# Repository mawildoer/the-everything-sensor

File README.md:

# The Everything Sensor!

A collective dev board for all the things our hearts desired.

## Features

 - BME280 (Temperature, Humidity, Pressure)
 - LIS2DH12TR (Accelerometer)
 - TMC2209 (Stepper Motor Driver)
 - HX711 (Load Cell Amplifier)
 - ATGM336H_5N31 (GPS)
 - SGP40_D_R4 (VOC Sensor)
 - MAX31856MUDT (Thermocouple Amplifier)
 - NAU7802 (Load Cell Amplifier)
 - TCA9548APWR (I2C Multiplexer)

 AND both an RP2040 and ESP32-S2 microcontroller!

## Getting Started

The `firmware` directory uses PlatformIO to support multiple build configurations, with different scripts to test different sensors.

## Known Bugs

### `1987a17`

- The `RP2040` USB balance resistors, meant to be `27Ω`, are actually `27kΩ`. This is fixed in the dependency for later builds
- The `TCA9548APWR` reset isn't tied high. This is fixed in the dependency for later builds

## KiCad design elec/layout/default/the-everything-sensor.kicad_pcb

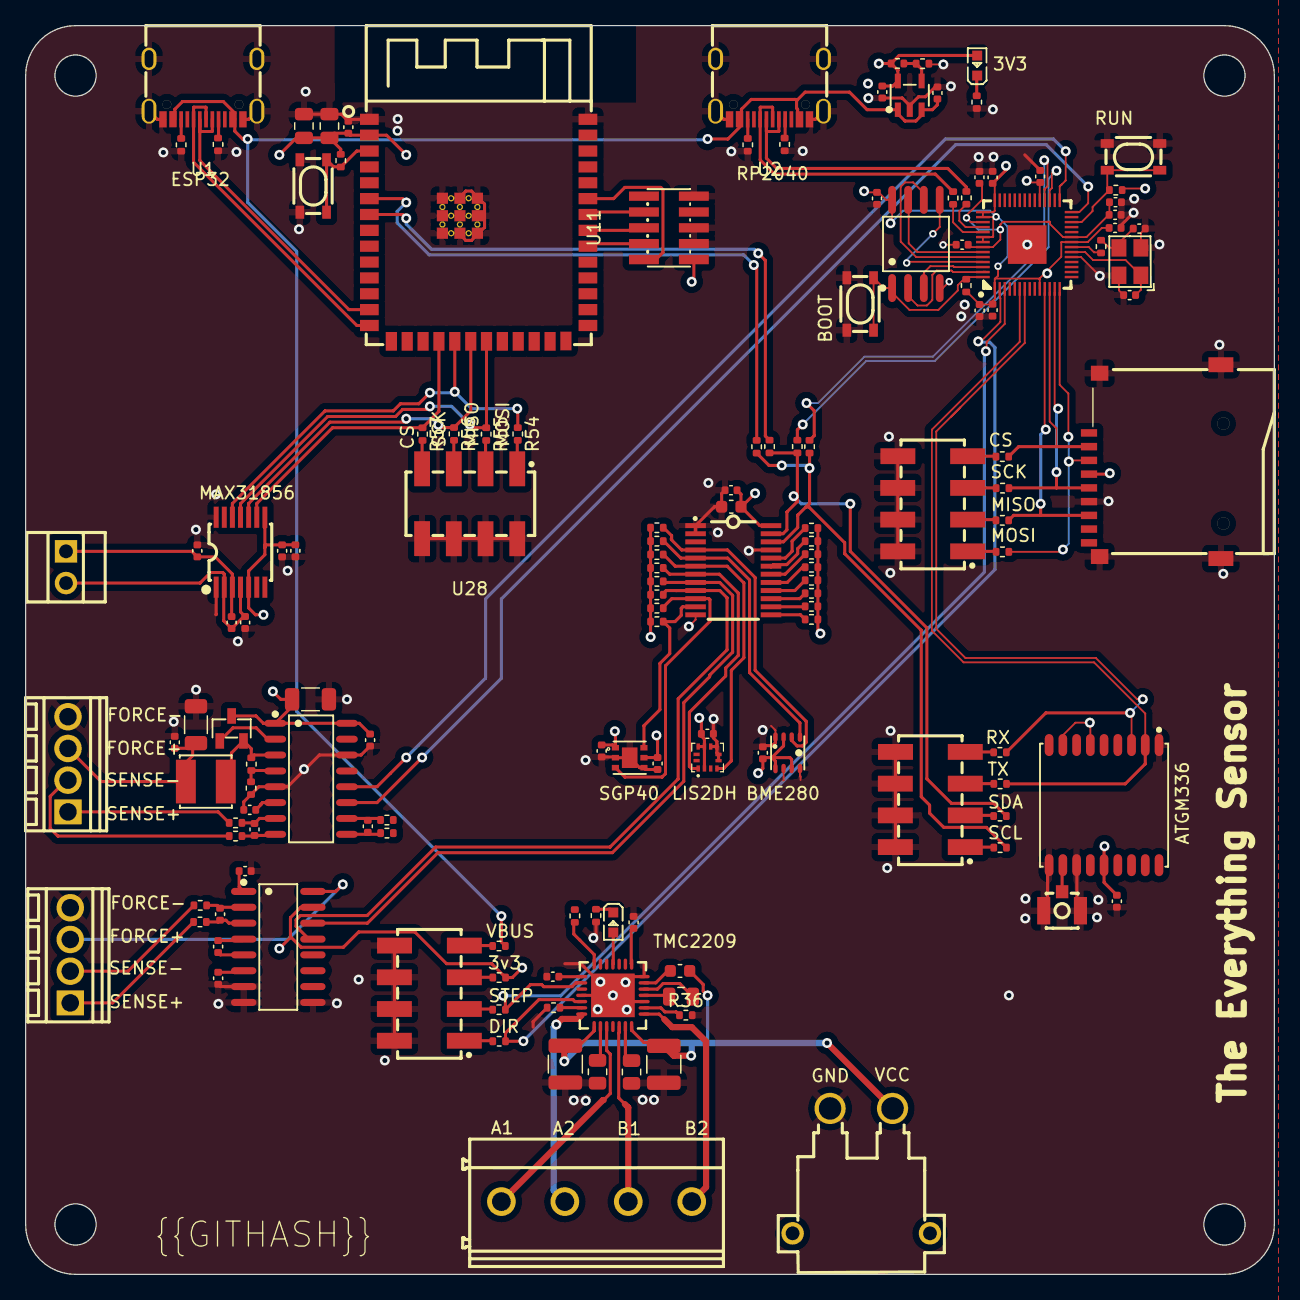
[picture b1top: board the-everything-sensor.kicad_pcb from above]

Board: 4 copper layers, 100.0 x 100.0 mm, 144 parts (0 on the bottom side), 123 nets.

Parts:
C1, C3, C4, C5, C6, C7, C11, C16, C17, C18, C19, C20, C22, C23, C24, C31, C35, C36, C37, C40, C43, C44, C45, C46: Multilayer Ceramic Capacitors MLCC - SMD/SMT 100n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; C0402
C2: Multilayer Ceramic Capacitors MLCC - SMD/SMT 2.2u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; C0603
C8: Multilayer Ceramic Capacitors MLCC - SMD/SMT 270p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; C0402
C9, C10, C21, C25, C26, C27, C34: Multilayer Ceramic Capacitors MLCC - SMD/SMT 1uF 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; C0402
C12, C13: Multilayer Ceramic Capacitors MLCC - SMD/SMT 10uF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; C0805
C14, C15: Multilayer Ceramic Capacitors MLCC - SMD/SMT 20pF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; C0402
C28, C29: Multilayer Ceramic Capacitors MLCC - SMD/SMT 2.2u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; C1210
C30: Multilayer Ceramic Capacitors MLCC - SMD/SMT 2.2u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; C0402
C32: Multilayer Ceramic Capacitors MLCC - SMD/SMT 22nF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; C0805
C33: Multilayer Ceramic Capacitors MLCC - SMD/SMT 100n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; C0603
C38, C39: Multilayer Ceramic Capacitors MLCC - SMD/SMT 22nF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; C0402
C41, C42: Multilayer Ceramic Capacitors MLCC - SMD/SMT 10uF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; C1206
J1: CONN-TH_XT30PW-M
L1: 1.23A 3.3uH ±20% SMD Power Inductors ROHS; ato-04ea3db2-4b2f-45a6-9113-aa1f8beaa754
LED1, LED2: LED0603-RD
Q1: SOT-23-3_L2.9-W1.3-P1.90-LS2.4-BR
R1, R2, R3, R4: Chip Resistor - Surface Mount 4.7KOhms ±5% 1/16W 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; R0402
R5, R6, R7, R8, R9, R10, R11, R12, R13, R14, R15, R16, R17, R18, R19, R20, R30, R34: Chip Resistor - Surface Mount 10KOhms ±5% 1/16W 0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; R0402
R21, R22: Chip Resistor - Surface Mount 51Ohms ±5% 1/16W 04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; R0402
R23, R29: Chip Resistor - Surface Mount 11KOhms ±5% 1/16W 0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; R0402
R24, R25, R31, R32: Chip Resistor - Surface Mount 0Ohms ±5% 1/16W 040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; R0402
R26, R42, R43, R44, R45, R46, R47, R48, R49, R50, R51, R52, R53, R54, R55, R56, R57: Chip Resistor - Surface Mount 1KOhms ±5% 1/16W 04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; R0402
R27, R28: Chip Resistor - Surface Mount 27KOhms ±5% 1/16W 0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; R0402
R33: Chip Resistor - Surface Mount 18KOhms ±5% 1/16W 0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; R0402
R35, R38: Chip Resistor - Surface Mount 120Ohms ±5% 1/16W 0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; R0402
R36, R41: Chip Resistor - Surface Mount 110KOhms ±5% 1/16W 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; R0402
R37: Chip Resistor - Surface Mount 1.1KOhms ±5% 1/16W 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; R0402
R39, R40: Chip Resistor - Surface Mount 0.12Ohms ±5% 1/8W 0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; R0805
R58: Chip Resistor - Surface Mount 20KOhms ±5% 1/16W 0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; R0402
R59: Chip Resistor - Surface Mount 8.2KOhms ±5% 1/16W 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; R0402
R60, R61, R62, R63: Chip Resistor - Surface Mount 100Ohms ±5% 1/16W 0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; R0402
U1, U2: USB-C-SMD_KH-TYPE-C-16P
U3: TSSOP-24_L7.8-W4.4-P0.65-LS6.4-BL
U4: LGA-8_BME280_BL
U5: LGA-12_L2.0-W2.0-P0.50-BL
U6: SOP-16_L9.9-W3.9-P1.27-LS6.0-BL
U7, U30: CONN-TH_XY308-2.54-4P
U8: DFN-6_L2.4-W2.4-P0.80-TL-EP
U9: WIRELM-SMD_ESP32-S3-WROOM-1
U10, U15, U16: KEY-SMD_4P-L4.2-W3.2-P2.20-LS4.6
U11: HDR-SMD_10P-P1.27-V-M-R2-C5-LS5.3
U12: LQFN-56_L7.0-W7.0-P0.4-EP
U13: OSC-SMD_4P-L3.2-W2.5-BL
U14: SOIC-8_L5.3-W5.3-P1.27-LS8.0-BL
U17: SOT-23-5_L3.0-W1.7-P0.95-LS2.8-BL
U18: QFN-28_L5.0-W5.0-P0.50-BL-EP
U19, U22, U25, U28: HDR-SMD_8P-P2.54-V-M-R2-C4-LS7.4
U20: CONN-TH_4P-P5.08_DIBO_DB128V-5.08
U21: TF-SMD_TF-01A
U23: GPSM-SMD_ATGM336H-TR
U24: IPEX-SMD_BWIPX-1-001E
U26: TSSOP-14_L5.0-W4.4-P0.65-LS6.4-BL
U27: CONN-TH_DB125-2.54-2P-GN
U29: SOP-16_L10.0-W3.9-P1.27-LS6.0-BL

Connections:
_1: R42.2, U19.1
_1-1: R46.2, U22.1
_1-2: R50.2, U25.1
_1-3: R54.2, U28.1
_3: R43.2, U19.3
_3-1: R47.2, U22.3
_3-2: R51.2, U25.3
_3-3: R55.2, U28.3
_5: R44.2, U19.5
_5-1: R48.2, U22.5
_5-2: R52.2, U25.5
_5-3: R56.2, U28.5
_5vout: C30.1, U18.8
_7-1: R45.2, U19.7
_7-2: R49.2, U22.7
_7-3: R53.2, U25.7
_7-4: R57.2, U28.7
a1: U18.24, U20.1
a2: U18.21, U20.2
avdd: L1.1, Q1.2, R58.1, U29.3
b1: U18.26, U20.3
b2: U18.1, U20.4
base: Q1.1, U29.2
bra: R39.1, U18.23
brb: R40.1, U18.27
cathode: LED1.1, R35.1
cathode-1: LED2.1, R38.1
cc1: R1.1, U1.A5
cc1-1: R3.1, U2.A5
cc2: R2.1, U1.B5
cc2-1: R4.1, U2.B5
clock: U12.28, U29.11
cpi: C32.2, U18.5
cpo: C32.1, U18.4
cs: R57.1, U9.18, U26.9
cs-1: R30.2, U12.56, U14.1, U16.1, U16.2
cs-2: R49.1, U12.12, U21.2
data: U12.29, U29.12
diag: LED2.2, U18.11
dir: R42.1, U12.2, U18.19
dm: U1.A7, U1.B7, U9.13
dm-1: R28.1, U2.A7, U2.B7
dp: U1.A6, U1.B6, U9.14
dp-1: R27.2, U2.A6, U2.B6
en: R23.2, U9.3, U10.1, U10.2
enn: R36.1, U18.2
gnd: C1.2, C2.2, C3.2, C4.2, C6.2, C7.2, C9.2, C10.2, C11.2, C12.2, C13.2, C14.2, C15.2, C16.2, C17.2, C18.2, C19.2, C20.2, C21.2, C22.2, C23.2, C24.2, C25.2, C26.2, C27.2, C28.2, C29.2, C30.2, C31.2, C34.2, C35.2, C36.2, C38.2, C39.2, C40.2, C41.2, C42.2, C43.2, C46.2, J1.1, R1.2, R2.2, R3.2, R4.2, R34.2, R35.2, R36.2, R38.2, R39.2, R40.2, R41.2, R59.2, U1.1, U1.2, U1.3, U1.4, U1.A1, U1.A12, U1.B1, U1.B12, U2.1, U2.2, U2.3, U2.4, U2.A1, U2.A12, U2.B1, U2.B12, U3.1, U3.2, U3.12, U3.21, U4.1, U4.5, U4.7, U5.5, U5.6, U5.7, U5.8, U6.7, U6.8, U6.9, U7.4, U8.2, U8.4, U8.7, U9.1, U9.40, U9.41, U10.3, U10.4, U11.3, U11.5, U11.9, U12.19, U12.57, U13.2, U13.4, U14.4, U15.3, U15.4, U16.3, U16.4, U17.2, U18.3, U18.7, U18.18, U18.29, U19.2, U19.4, U19.6, U19.8, U21.6, U21.10, U21.11, U21.12, U21.13, U22.2, U22.4, U22.6, U22.8, U23.1, U23.10, U23.12, U24.2, U24.3, U25.2, U25.4, U25.6, U25.8, U26.1, U26.14, U28.2, U28.4, U28.6, U28.8, U29.5, U29.14, U30.4
inna: C44.2, R61.1, U29.7
innb: C45.2, R63.1, U29.9
inpa: C44.1, R60.2, U29.8
inpb: C45.1, R62.2, U29.10
io0-1: U12.53, U14.5
io1-1: U12.55, U14.2
io2-1: U12.54, U14.3
io3-1: U12.51, U14.7
miso: R55.1, U9.21, U26.11
miso-1: R47.1, U12.11, U21.7
mosi: R54.1, U9.19, U26.12
mosi-1: R46.1, U12.14, U21.3
n: R21.2, U7.2
n-1: C37.2, C39.1, U26.2, U26.4, U27.2
n-2: R60.1, U30.2
out: C15.1, R26.2, U13.3
out-1: R33.2, R34.1, U17.4
p: R22.2, U7.1
p-1: C37.1, C38.1, U26.3, U27.1
p-2: R61.2, U30.1
pdn_uart: R37.2, U18.14
refp: C7.1, U6.1
rf_in: U23.11, U24.1
run: R29.2, U12.26, U15.1, U15.2
rx: R53.1, U12.7, U23.3
sck: R56.1, U9.20, U26.10
sck-1: U12.52, U14.6
sck-2: R48.1, U12.13, U21.5
scl: R25.1, R32.1, R50.1, U3.22
scl-1: R5.2, U3.5, U4.4
scl-2: R7.2, U3.7, U5.1
scl-3: R9.2, U3.9, U6.13
scl-4: R11.2, U3.11, U8.6
scl-5: R13.2, U3.14
scl-6: R15.2, U3.16
scl-7: R17.2, U3.18
scl-8: R19.2, U3.20
scl-9: R25.2, U9.6
scl-10: R32.2, U12.32
sda: R24.1, R31.1, R51.1, U3.23
sda-1: R6.2, U3.4, U4.3
sda-2: R8.2, U3.6, U5.4
sda-3: R10.2, U3.8, U6.14
sda-4: R12.2, U3.10, U8.3
sda-5: R14.2, U3.13
sda-6: R16.2, U3.15
sda-7: R18.2, U3.17
sda-8: R20.2, U3.19
sda-9: R24.2, U9.7
sda-10: R31.2, U12.31
stdby: R41.1, U18.20
step: R43.1, U12.3, U18.16
tck: U9.32, U11.4
tdi: U9.34, U11.8
tdo: U9.33, U11.6
tms: U9.35, U11.2
tx: R52.1, U12.6, U23.2
usb_dm: R28.2, U12.46
usb_dp: R27.1, U12.47
vbg: C6.1, U6.6
vbg-1: C46.1, U29.6
vcc: C1.1, C2.1, C3.1, C4.1, C9.1, C10.1, C11.1, C12.1, C13.1, C16.1, C17.1, C18.1, C19.1, C20.1, C21.1, C27.1, C34.1, C35.1, C36.1, C40.1, C41.1, LED1.2, Q1.3, R5.1, R6.1, R7.1, R8.1, R9.1, R10.1, R11.1, R12.1, R13.1, R14.1, R15.1, R16.1, R17.1, R18.1, R19.1, R20.1, R23.1, R29.1, R30.1, R33.1, R44.1, U3.24, U4.2, U4.6, U4.8, U5.2, U5.9, U5.10, U6.15, U8.1, U8.5, U9.2, U11.1, U12.1, U12.10, U12.22, U12.33, U12.42, U12.43, U12.44, U12.48, U12.49, U14.8, U17.5, U21.4, U23.6, U23.8, U23.14, U26.5, U26.8, U29.1, U29.16
vcc-1: C26.1, R45.1, U1.A4, U1.A9, U1.B4, U1.B9, U2.A4, U2.A9, U2.B4, U2.B9, U17.1, U17.3
vcc-2: U6.16, U7.3
vcc-4: C22.1, C23.1, C24.1, C25.1, U12.23, U12.45, U12.50
vcc-5: C28.1, C29.1, C33.2, J1.2, U18.22, U18.28
vcc-6: C42.1, C43.1, L1.2, U30.3
vcc_io: C31.1, U18.15
vcp: C33.1, U18.6
vfb: R58.2, R59.1, U29.4
vin1n: C5.1, R21.1, U6.2
vin1p: C5.2, R22.1, U6.3
vin2n: C8.1, U6.4
vin2p: C8.2, U6.5
xin-1: C14.1, U12.20, U13.1
xout-1: R26.1, U12.21

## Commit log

2024-02-12 Configure project
2024-02-13 made some things
2024-02-15 layout complete
2024-02-15 cleanup ato yaml
2024-02-15 minor bug fixes
2024-02-15 adding programming header to deps
2024-02-15 cleanup silkscreen
2024-05-09 Lock the esp32 dep to where they were manufactures in 1987a17
2024-05-09 Make I2C scanner
2024-05-09 Add builds for bringup firmware
2024-05-09 Add bug log
